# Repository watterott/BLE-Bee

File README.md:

# BLE-Bee
XBee footprint compatible Bluetooth Low Energy (BLE) Module.

* u-blox NINA-B3 BLE (Bluetooth Low Energy) module
* UART interface
* XBee compatible Pinout (3.3V)
* Open-Source and released under the [Creative Commons Attribution Share-Alike License](https://creativecommons.org/licenses/by-sa/4.0/).
* **[Documentation on learn.watterott.com](https://learn.watterott.com)**

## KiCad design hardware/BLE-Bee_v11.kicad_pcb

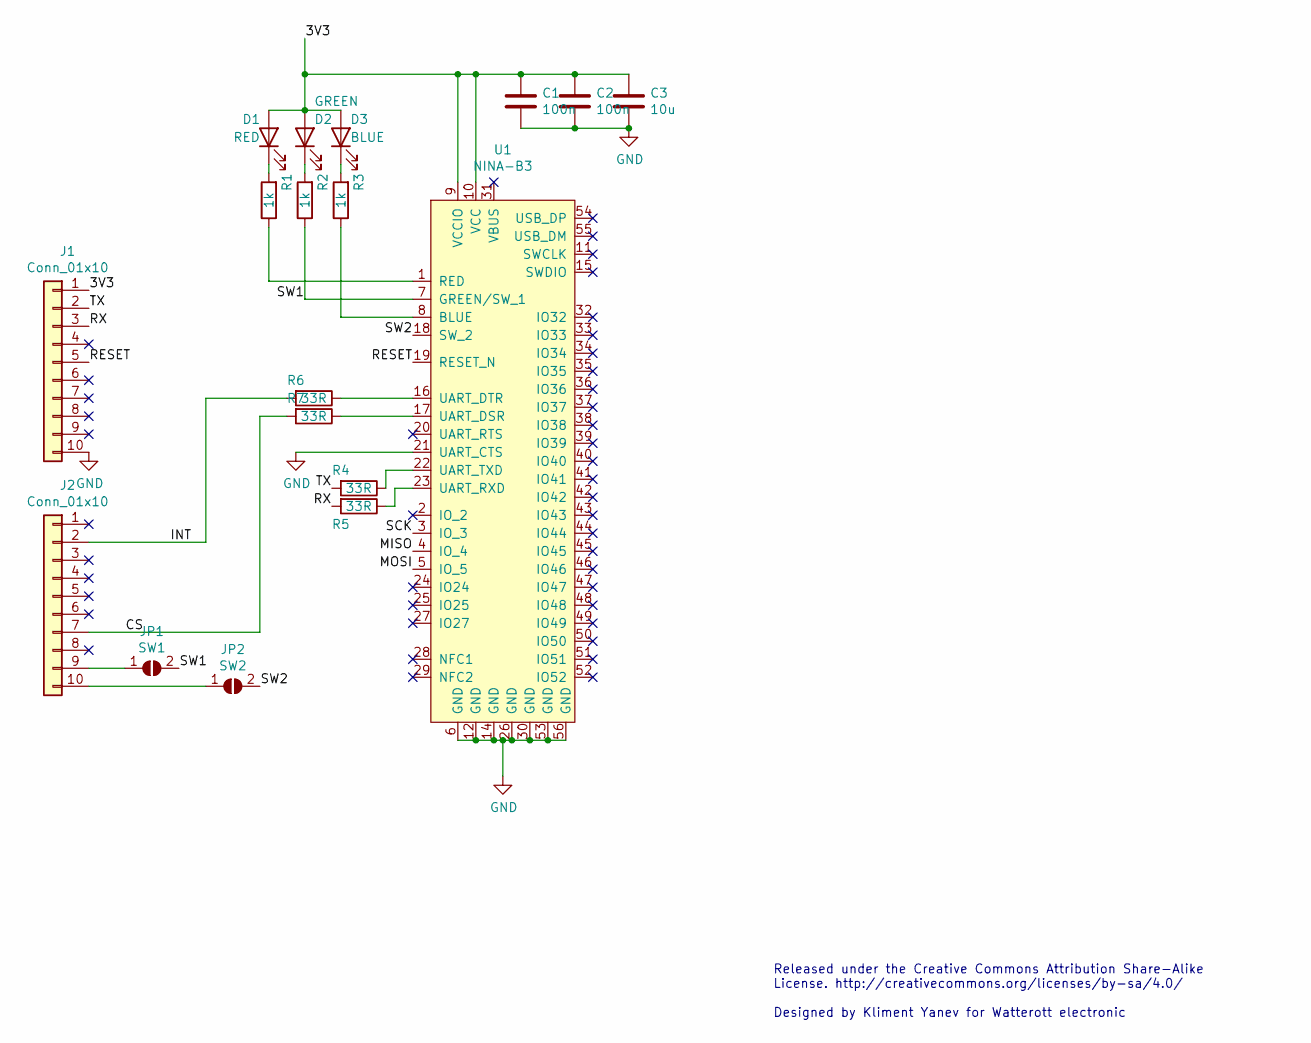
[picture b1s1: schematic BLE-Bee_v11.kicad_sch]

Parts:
C1, C2: 100n; C_0603_1608Metric
C3: 10u; C_0805_2012Metric
D1: RED; LED_0603_1608Metric
D2: GREEN; LED_0603_1608Metric
D3: BLUE; LED_0603_1608Metric
J1, J2: Conn_01x10; PinHeader_1x10_P2.00mm_Vertical
JP1: SW1; SolderJumper-2_P1.3mm_Open_RoundedPad1.0x1.5mm
JP2: SW2; SolderJumper-2_P1.3mm_Open_RoundedPad1.0x1.5mm
R1, R2, R3: 1k; R_0603_1608Metric
R4, R5, R6, R7: 33R; R_0603_1608Metric
U1: NINA-B3; NINA-B3x2

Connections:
/3V3: C1.1, C2.1, C3.1, D1.2 (A), D2.2 (A), D3.2 (A), J1.1, U1.9 (VCCIO), U1.10 (VCC)
/CS: J2.7, R7.2
/INT: J2.2, R6.2
/MISO: U1.4 (IO_4)
/MOSI: U1.5 (IO_5)
/RESET: J1.5, U1.19 (RESET_N)
/RX: J1.3, R5.2
/SCK: U1.3 (IO_3)
/SW1: JP1.2 (B), R2.1, U1.7 (GREEN/SW_1)
/SW2: JP2.2 (B), U1.18 (SW_2)
/TX: J1.2, R4.2
GND: C1.2, C2.2, C3.2, J1.10, U1.6 (GND), U1.12 (GND), U1.14 (GND), U1.21 (UART_CTS), U1.26 (GND), U1.30 (GND), U1.53 (GND), U1.56 (GND)
unnamed: D1.1 (K), R1.2
unnamed: D2.1 (K), R2.2
unnamed: D3.1 (K), R3.2
unnamed: J2.9, JP1.1 (A)
unnamed: J2.10, JP2.1 (A)
unnamed: R1.1, U1.1 (RED)
unnamed: R3.1, U1.8 (BLUE)
unnamed: R4.1, U1.22 (UART_TXD)
unnamed: R5.1, U1.23 (UART_RXD)
unnamed: R6.1, U1.16 (UART_DTR)
unnamed: R7.1, U1.17 (UART_DSR)

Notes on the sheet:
Released under the Creative Commons Attribution Share-Alike License. http://creativecommons.org/licenses/by-sa/4.0/ Designed by Kliment Yanev for Watterott electronic

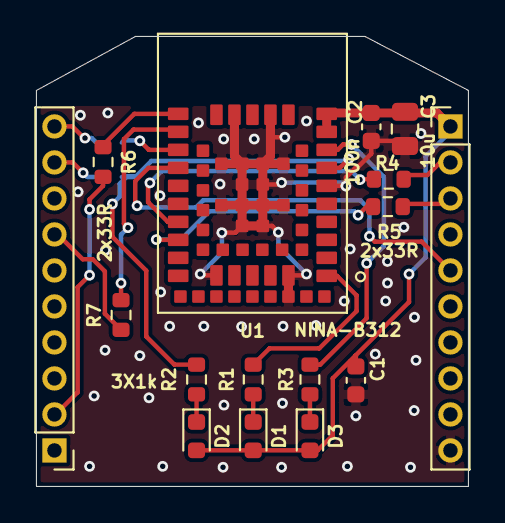
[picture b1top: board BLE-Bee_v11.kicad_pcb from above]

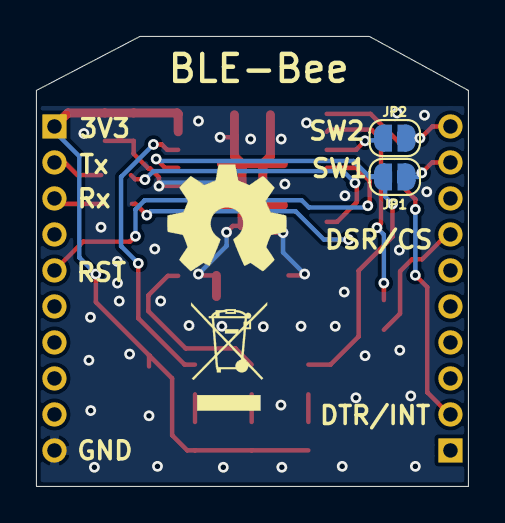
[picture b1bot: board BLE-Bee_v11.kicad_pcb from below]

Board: 2 copper layers, 24.0 x 25.0 mm, 18 parts (2 on the bottom side), 20 nets.

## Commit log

2021-08-27 added readme
2022-07-01 added layout and schematics
